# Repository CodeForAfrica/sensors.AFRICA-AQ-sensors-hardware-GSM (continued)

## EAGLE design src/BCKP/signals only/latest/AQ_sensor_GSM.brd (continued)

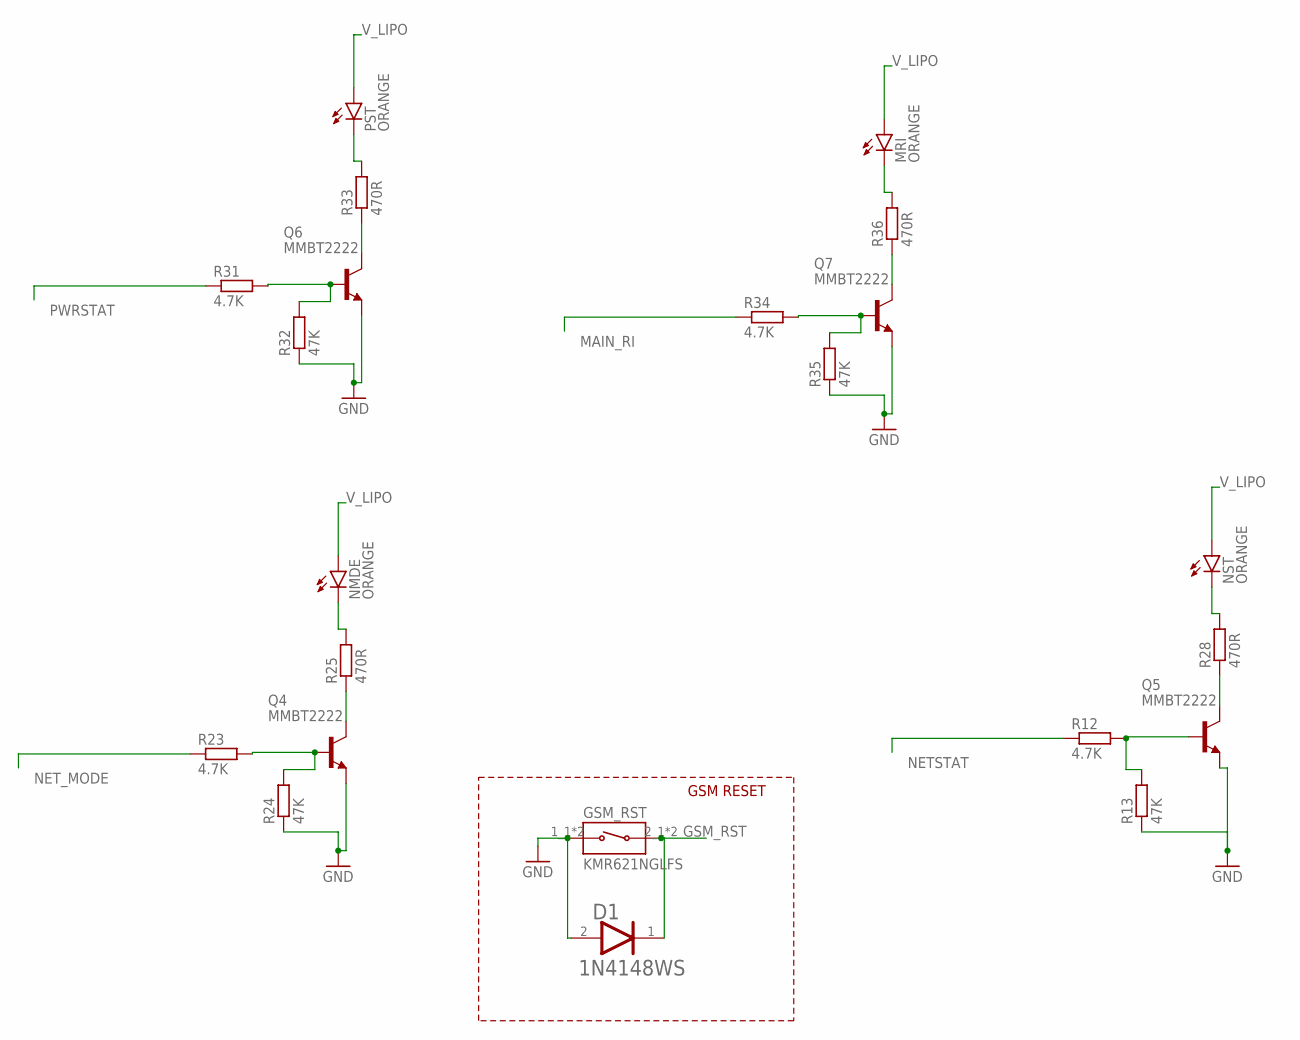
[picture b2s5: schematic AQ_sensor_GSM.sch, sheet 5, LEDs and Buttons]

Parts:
D1: ON_SEMI_1N4148WSON_SEMI_1N4148WS_0_0; ON_SEMI_1N4148WS_0
GSM_RST: KMR621NGLFS; SW_KMR621NGLFS
MRI: ORANGE; CHIP-LED0603
NMDE: ORANGE; CHIP-LED0603
NST: ORANGE; CHIP-LED0603
PST: ORANGE; CHIP-LED0603
Q4, Q5, Q6, Q7: MMBT2222; SOT23-BEC
R12, R23, R31, R34: 4.7K; R0603
R13, R24, R32, R35: 47K; R0603
R25, R28, R33, R36: 470R; R0603

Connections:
GND: D1.2 (ANODE), GSM_RST.1_1 (1), GSM_RST.1_2 (1), Q4.E, Q5.E, Q6.E, Q7.E, R13.1, R24.1, R32.1, R35.1; also elsewhere on the board
GSM_RST: D1.1 (CATHODE), GSM_RST.2_1 (2), GSM_RST.2_2 (2); also elsewhere on the board
MAIN_RI: R34.1; also elsewhere on the board
unnamed: Q5.B, R12.2, R13.2
unnamed: Q4.B, R23.2, R24.2
unnamed: Q6.B, R31.2, R32.2
unnamed: Q4.C, R25.1
unnamed: NMDE.C, R25.2
unnamed: Q6.C, R33.1
unnamed: Q5.C, R28.1
unnamed: NST.C, R28.2
unnamed: PST.C, R33.2
unnamed: Q7.B, R34.2, R35.2
unnamed: Q7.C, R36.1
unnamed: MRI.C, R36.2
NETSTAT: R12.1; also elsewhere on the board
NET_MODE: R23.1; also elsewhere on the board
PWRSTAT: R31.1; also elsewhere on the board
V_LIPO: MRI.A, NMDE.A, NST.A, PST.A; also elsewhere on the board

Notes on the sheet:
GSM RESET

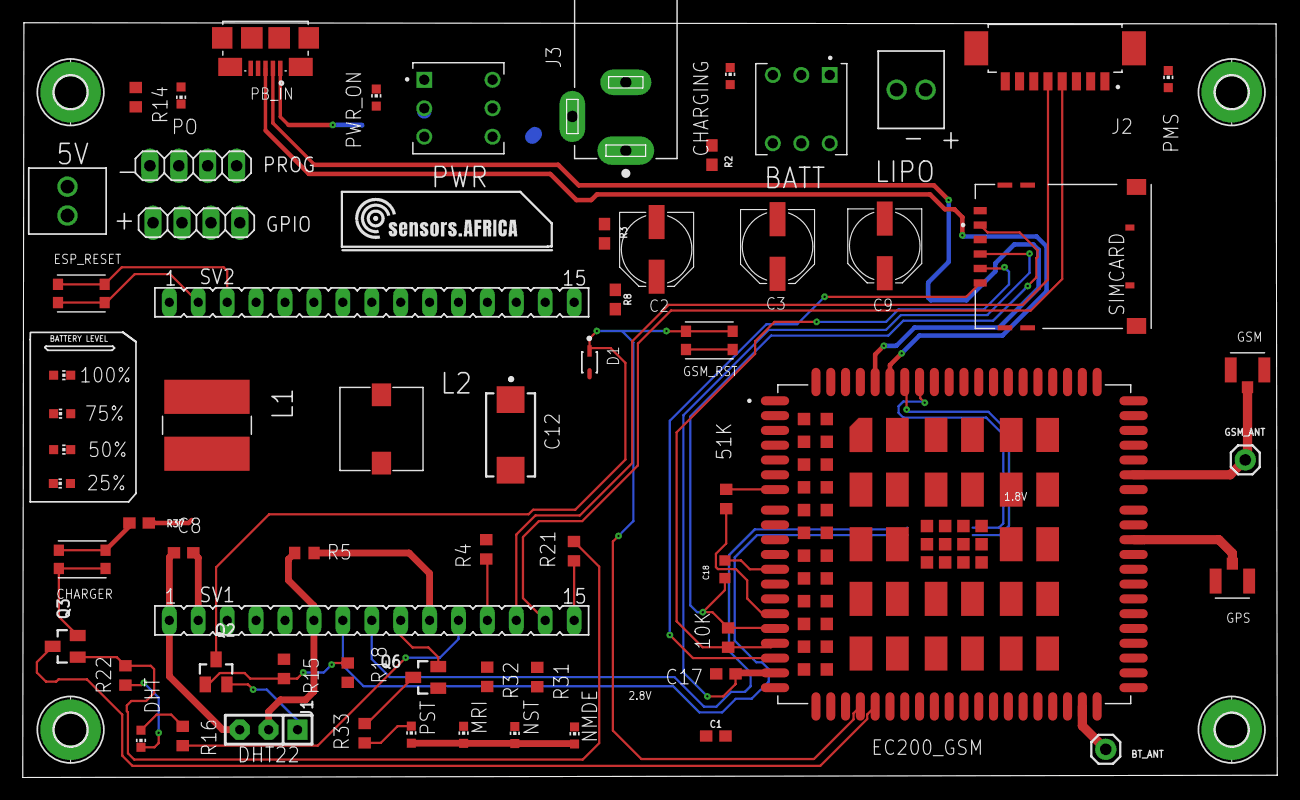
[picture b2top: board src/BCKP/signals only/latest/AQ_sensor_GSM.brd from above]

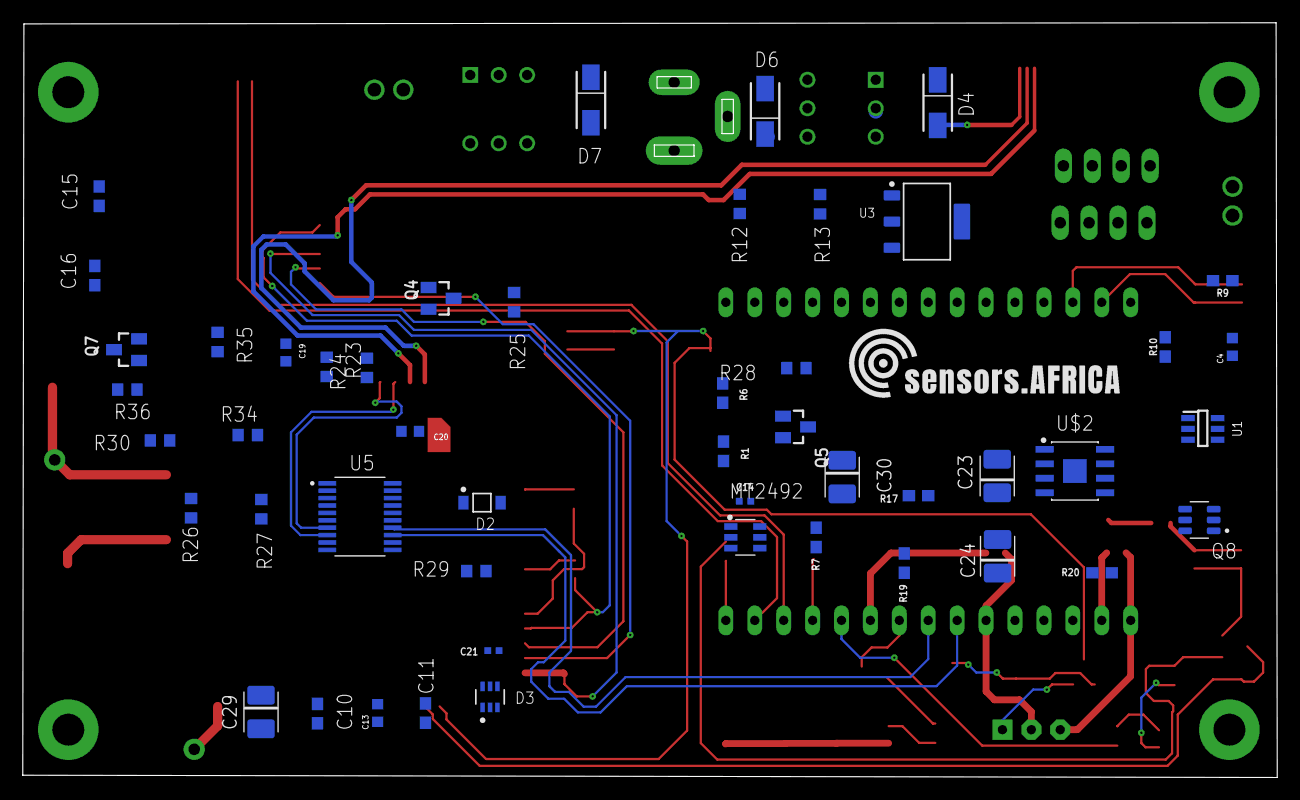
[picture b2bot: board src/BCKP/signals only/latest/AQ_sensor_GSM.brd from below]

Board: 2 copper layers, 110.2 x 66.3 mm, 118 parts (49 on the bottom side), 92 nets.

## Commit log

2023-09-25 Add gitignore file
2023-09-25 Revert "Fix/swap dht pms locations"
2024-01-18 Added buck Converter circuitry
2024-01-18 Added Nano sim adapter
2024-01-19 Added GNSS Antenna, reconfigured the PCB Layout
2024-01-19 Added Bluetooth and Wifi Antenna
2024-01-19 Updated GSM antenna positions, pms connector, USB, and battery connector positions
2024-01-20 Added dC jack
2024-01-20 PCB Routed
2024-01-23 Rearrange USB port and DC jack
2024-01-25 Added internal gsm Antenna
2024-02-08 Routed
2024-02-08 Resolved missing Airwires
2024-02-08 AQ_sensor_GSM_2024-02-08_Y5
2024-02-08 Update Power trace width
2024-02-09 Revision without Sd Card
2024-02-16 Resolved Inconsistency Errors. Not Routed
2024-02-16 Completed Autorouting and TraceWidth Modification. No GND Plane
2024-02-23 Replaced battery connector with 5.08mm terminal block
2024-05-22 Added Lipo charging system
2024-05-22 Reordered components on the PCB, added Lipo charging circuit, added Charging level inidcator LED Bar.
2024-06-05 Trace Width updated
2024-06-11 Routed - Minus DW01
2024-07-15 JLCPCB V2
2024-08-27 Replaced 5v regulator to lm7805
2024-09-08 Nigeria Order, PCB Routed
2024-12-02 Differential Pair routing
2024-12-03 Routed V1
2025-01-22 December 2024 Manufacturing Batch.
2025-02-27 Add git ignore file
    Untrack Eagle temporary backup files
2025-03-13 Fix #9: Correct pin Mapping
    SD_MOSI, SD_MISO, PMS_RX, and PMS_TX
2025-10-14 Add Second ESP Reset Button
    Remove Some ERC Warnings
2025-10-16 Fix DRC errors: add NC symbol and resolve missing junction warnings
    Create a Not Connected symbol in library list
2026-01-21 Refactor: V4 board
2026-01-21 Redundant:ignore temp board files
2026-01-22 EC200U V5 dir
2026-01-27 Add Quectel Version I design
2026-01-27 Add Quectel EC200U version 2
2026-01-27 Add Quectel EC200U version 3
2026-02-02 V5 revised
2026-02-02 V5 images
2026-02-02 V4 revised with images
2026-02-03 V3 revised
2026-02-03 V3 images
2026-02-03 V2 revised
2026-02-03 V1 revised
2026-02-03 Restore v2
2026-02-03 Refactor: Create separate board dirs for NodeMCU and ESP32S3
2026-02-03 CHANGELOG: NodeMCU Quectel boards
2026-02-03 CHANGELOG: ESP32S3 Quectel boards
2026-04-20 Added TP4056, TPS63802DLAR buck boost converter for the 5V and 4.0V rails
2026-04-22 Routing in Progress
2026-04-23 90% routed
2026-04-23 100% routed Minus Board Outline
2026-04-24 Resolved multiple shared output pins
2026-04-27 Route PCB 100%
    Add 5V buck boost converter for charging Side
    Add boost converter for 4.0V voltage rail
    Add 5V Boost converter for the 5V rail
    Add 3.3V LDO to power MCU
2026-04-29 Add 1.8V LDO, EC200UCN Firmware Boot Circuitry, GSM Patch Antenna
2026-04-30 Add Ground clearance for the antenna
2026-04-30 Update Sheet frames
2026-04-30 Fix #13: Swap SD SPI MISO and MOSI lines
2026-04-30 Add USB C A5 (CC1) to GND via 5k1 Resistor - B5 (CC2) to GND via another 5k1 Resistor
2026-05-04 Add 2G, 3G, and 4G GSM Antenna
    Add Pi network for impendance matching
